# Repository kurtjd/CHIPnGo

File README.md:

# CHIPnGo
|Current Status|
|--------------|
||

Recently I've taken a serious interest in embedded development, so I decided for my first project I would attempt to port my [CHIP-8 emulator](https://github.com/kurtjd/jaxe) to a STM32 microcontroller in order to eventually build a CHIP-8 hand-held gaming console. Since this is being done as a learning experience, I also decided I would do this bare-metal with no libraries and write all drivers from scratch. While this is proving to be slow and extremely frustrating at times, it has also been very insightful and I've already learned a ton in such a short time.

[See it in action!](https://www.youtube.com/watch?v=SVods0DDVes)

## Build Guide
If you are interested in building your own CHIPnGo, check out [this guide](https://kurtjd.github.io/2022/07/16/chipngo-build-guide/).

## Development Blog
If you are interested in reading about my development of the project, some challenges I faced, and the bone-headed design decisions I made along the way due to my inexperience, check out my [dev blog](https://kurtjd.github.io/2022/07/08/chipngo-dev-1-intro/).

## Features
- Fully supports all CHIP-8 and S-CHIP ROMs
- LCD graphical display
- Four directional buttons and two action buttons
- Piezo buzzer for simple tone generation
- SD card reader for quick loading of any CHIP-8 ROM
- Battery power
- [Desktop application to manage ROMs on an SD card (aka game cartridge)](tools/cartridge8/)

## ToDo
- Improve startup menu for user to select ROM via SD card (make a bit more pretty)
- Improve startup splash screen (want something cool and animated)
- Iron out minor firmware bugs

## Limitations
Although my original emulator also has full support for XO-CHIP roms, I decided to focus on just CHIP-8 and S-CHIP for now for several reasons:
- XO-CHIP ROMs expect up to 64kb of memory, as opposed to 4kb expected by original CHIP-8 ROMs.
- XO-CHIP supports up to three colors, which would mean needing to move beyond a simple monochrome display.
- XO-CHIP supports variable frequencies/tones whereas CHIP-8 ROMs can only produce a single frequency, which makes handling sound simple.

CHIP-8 supports 16 keys for input, however for design purposes, the console only has 6 buttons.
However, most games only use a few buttons so this isn't too much of an issue.

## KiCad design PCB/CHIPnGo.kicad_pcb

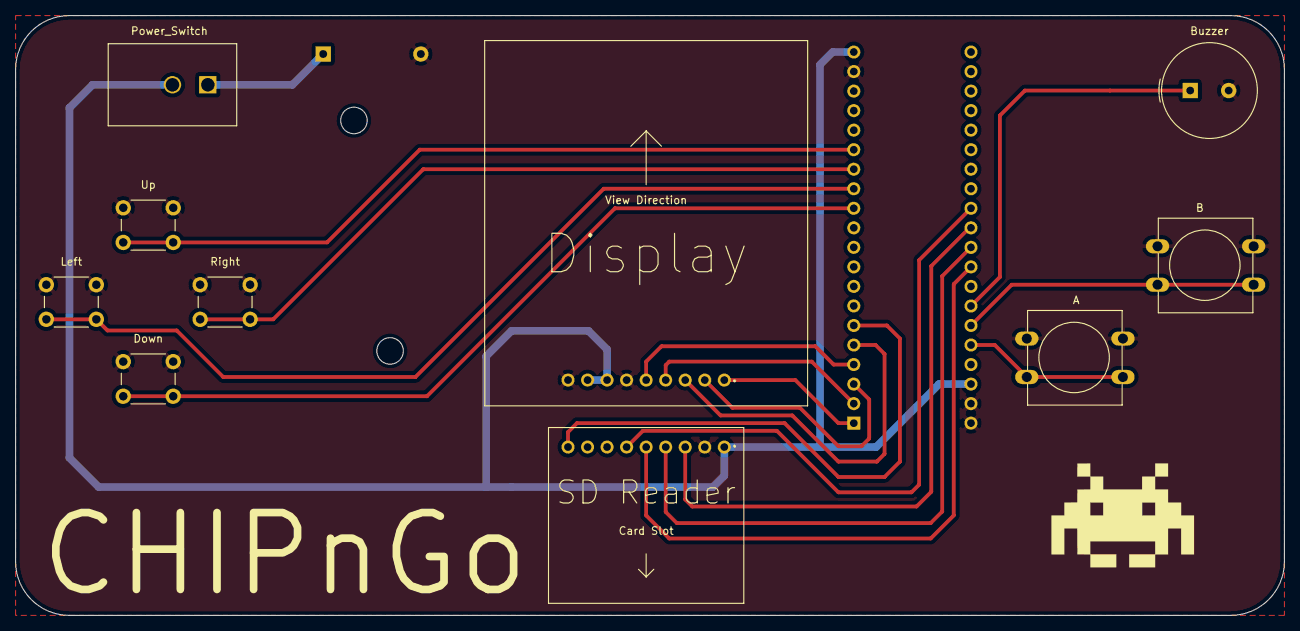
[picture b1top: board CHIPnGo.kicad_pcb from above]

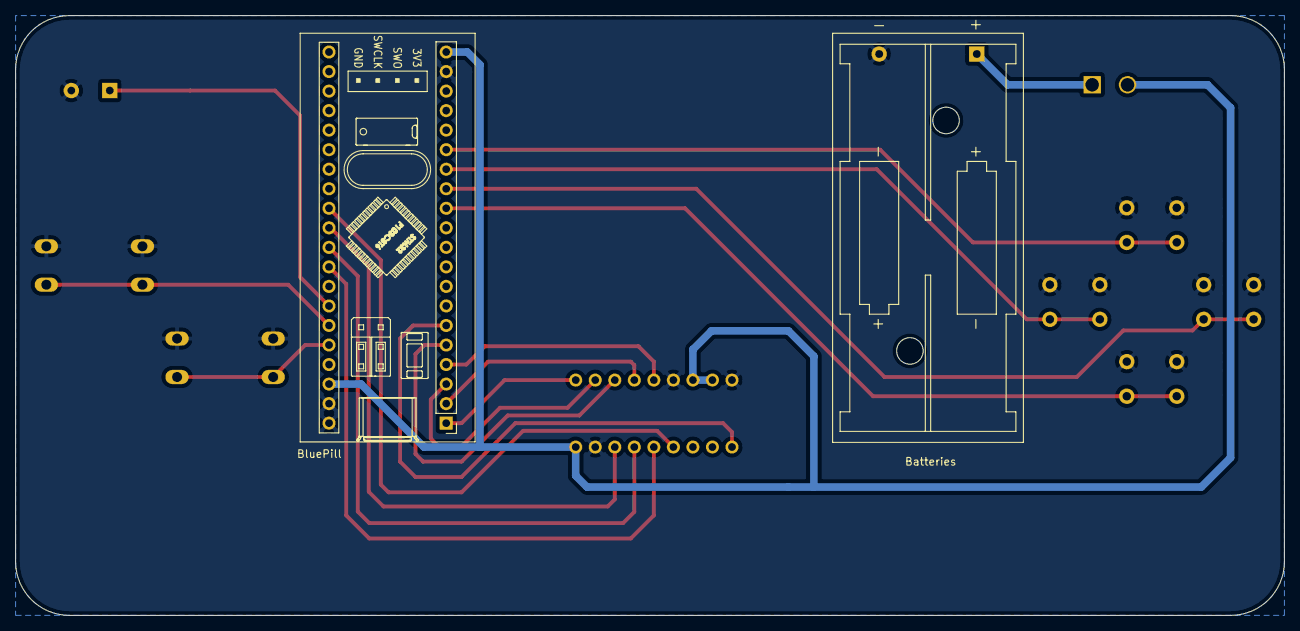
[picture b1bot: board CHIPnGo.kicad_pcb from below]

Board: 2 copper layers, 165.0 x 78.0 mm, 12 parts (2 on the bottom side), 20 nets.

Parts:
A: A_Btn; SW_PUSH-12mm
B: B_Btn; SW_PUSH-12mm
Batteries: Batteries; BatteryHolder_Keystone_2468_2xAAA
BluePill: STM32_BluePill; YAAJ_BluePill_1
Buzzer: Piezo_Buzzer; Buzzer_TDK_PS1240P02BT_D12.2mm_H6.5mm
Display: ERM12864-8_Display; ERM12864
Down: Down_Btn; SW_PUSH_6mm_H5mm
Left: Left_Btn; SW_PUSH_6mm_H5mm
Power_Switch: Power_Switch; GF-123-0054
Right: Right_Btn; SW_PUSH_6mm_H5mm
SD Reader: Adafruit_MicroSD_Breakout; Adafruit_SD_Reader
Up: Up_Btn; SW_PUSH_6mm_H5mm

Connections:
+3V3: BluePill.20, BluePill.38, Display.7, Display.8, Power_Switch.2, SD Reader.1
/Card_Det: BluePill.6, SD Reader.9
GND: A.2, B.2, Batteries.2, BluePill.19, BluePill.39, BluePill.40, Buzzer.2, Display.6, Display.9, Down.1, Left.1, Right.1, SD Reader.2, Up.1
unnamed: Batteries.1, Power_Switch.1
unnamed: BluePill.34, Buzzer.1
unnamed: BluePill.13, Left.2
unnamed: BluePill.12, Down.2
unnamed: BluePill.15, Up.2
unnamed: BluePill.14, Right.2
unnamed: A.1, BluePill.36
unnamed: B.1, BluePill.35
unnamed: BluePill.30, SD Reader.3
unnamed: BluePill.31, SD Reader.4
unnamed: BluePill.32, SD Reader.5
unnamed: BluePill.29, SD Reader.6
unnamed: BluePill.1, Display.1
unnamed: BluePill.2, Display.4
unnamed: BluePill.3, Display.2
unnamed: BluePill.4, Display.5
unnamed: BluePill.5, Display.3

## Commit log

2022-04-11 Add license
2022-04-11 Fix .gitignore
2022-04-11 Add current status image
2022-04-11 Begin writing SPI driver
2022-04-15 Reorganizing GPIO
2022-04-15 Factor out some GPIO
2022-04-17 SPI Stuff
2022-04-22 Create basic PWM driver
2022-04-22 Add sound support (via PWM to a piezo buzzer)
2022-04-22 Add status update
2022-04-22 Update README.md
    Remove add sound from TODO (complete)
2022-04-25 Change button to pin config
2022-04-25 Begin writing sd driver
2022-05-07 Implement basic display driver
2022-05-14 Add basic font and splash screen
2022-05-15 Lower SPI speed to seemingly fix display corruption
2022-05-26 Implement SD initialization sequence
2022-05-27 Implement SD read block
2022-05-27 Implement read multiple blocks
2022-05-28 Implement sd write single block
2022-05-28 Implement read single ROM from SD
2022-05-28 Implement rudimentary ROM selection menu
2022-05-29 Add quirk parsing and fix input bug
2022-05-29 Implement user flags save/load from SD
2022-06-01 Begin implementing cartridge hacker
2022-06-01 Fix seek_rom bug
2022-06-02 Implement rough working version of Cartridge Hacker
2022-06-02 Add DEADBEEF
2022-06-02 Finish implementing Cartridge8 functionality
2022-06-02 Add Cartridge8 screenshots
2022-06-02 Add requirements.txt
2022-06-04 Implement startup SD checks
2022-06-04 Handle no ROMs on SD
2022-06-04 Implement SD initialize timeout
2022-06-05 Make input interrupt-driven as opposed to polling
2022-06-05 Change clock to use timer instead of systick
2022-06-05 Simplify timer
2022-06-06 Autoformat
2022-06-06 Fix compiler error
2022-06-12 Handle exit command properly and update README
2022-06-12 Handle exit properly
2022-06-14 Update status image
2022-06-15 Swap position of bluepill and buttons
2022-06-20 Change button input pins for cleaner PCB traces
2022-06-25 Change pins for SD and display for better trace routing
2022-07-03 Add PCB image
2022-07-16 Add platformio.ini
2022-07-17 Add PCB files
2022-07-24 Fix SD bug
2023-08-13 Remove left over debugging code

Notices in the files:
PCB/CHIPnGo.kicad_pcb:
License: MIT
parts and their libraries:
Copyright 2021 Accelerated Designs. All rights reserved.
